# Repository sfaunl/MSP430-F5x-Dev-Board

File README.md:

MSP430-F5x-Dev-Board
====================

MSP430 5 Series Development Board

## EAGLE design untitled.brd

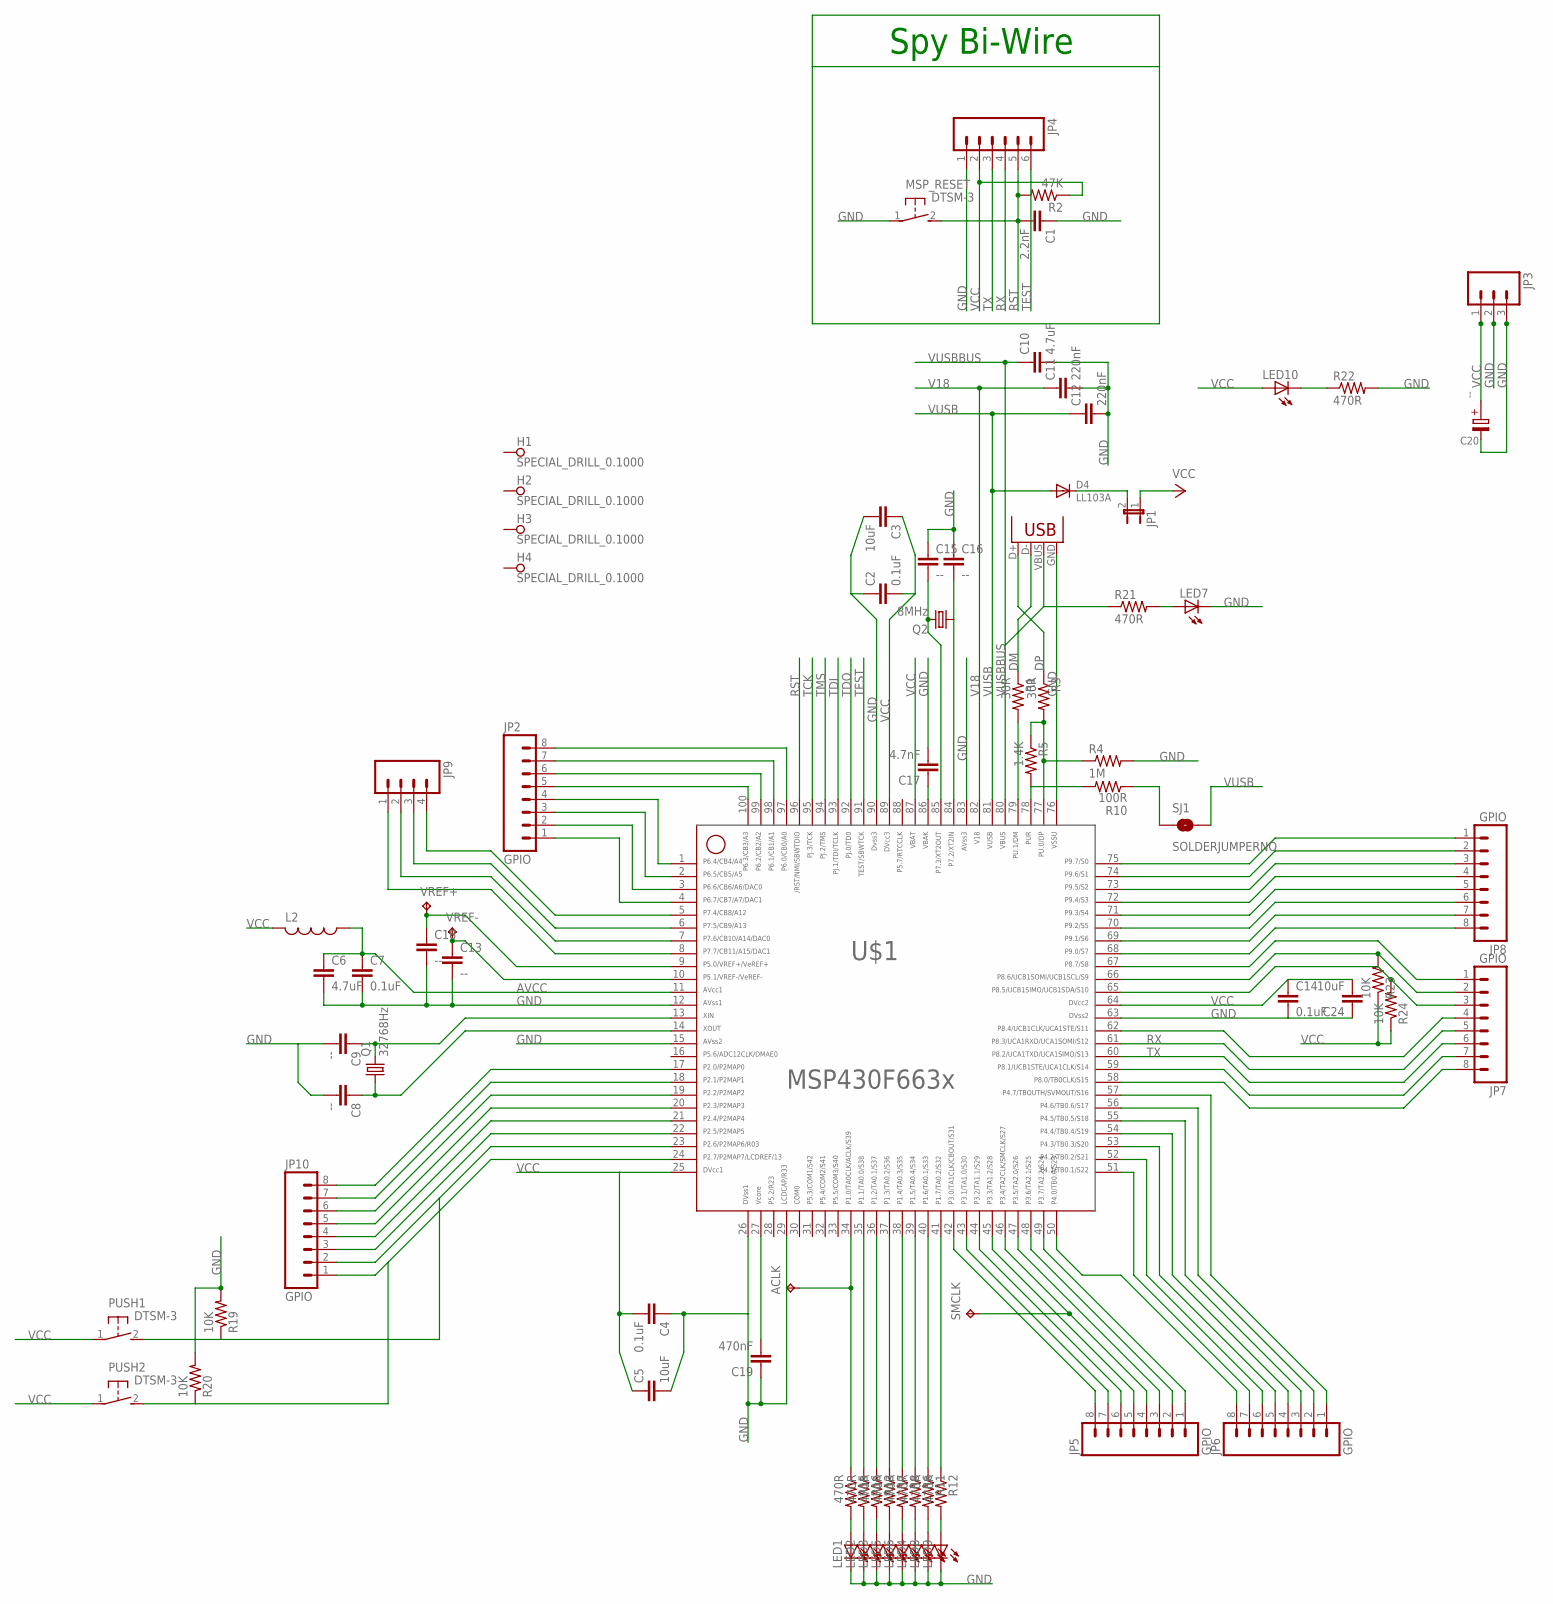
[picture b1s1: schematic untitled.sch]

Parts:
ACLK: TPB1,27; B1,27
C1: 2.2nF; 0805
C2, C4, C7, C14: 0.1uF; 0805
C3, C5, C24: 10uF; 0805
C6, C10: 4.7uF; 0805
C8, C9, C13, C15, C16, C18: --; 0805
C11, C12: 220nF; 0805
C17: 4.7nF; 0805
C19: 470nF; 0805
C20: --; 1210ELKO
D4: LL103A; SOD-80
H1, H2, H3, H4: SPECIAL_DRILL_0.1000; PAD_0.1000
JP1: JP1E; JP1
JP2, JP5, JP6, JP7, JP8, JP10: GPIO; 1X08
JP3: M03PTH; 1X03
JP4: M06SIP; 1X06
JP9: M04PTH; 1X04
L2: L-USL2012C; L2012C
LED1, LED2, LED3, LED4, LED5, LED6, LED7, LED8, LED9, LED10: LEDCHIPLED_0805; CHIPLED_0805
MSP_RESET: DTSM-3
PUSH1, PUSH2: DTSM-3
Q1: 32768Hz; TC26H
Q2: 8MHz; HC49U-V
R1, R3: 30R; M0805
R2: 47K; M0805
R4: 1M; M0805
R5: 1.4K; M0805
R6, R7, R8, R11, R12, R13, R15, R16, R21, R22: 470R; R0603
R10: 100R; R0603
R19, R20, R23, R24: 10K; M0805
SJ1: SOLDERJUMPERNO; SJ_2S-NO
SMCLK: TPB1,27; B1,27
U$1: F66XX---PZ100; PZ100
VREF+: TPB1,27; B1,27
VREF-: TPB1,27; B1,27
X1: USBSMD; USB-MINIB

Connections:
AVCC: C6.1, C7.1, L2.1, U$1.11
DM: R1.1, X1.D-
DP: R3.1, X1.D+
GND: C1.1, C2.1, C3.2, C4.1, C5.2, C6.2, C7.2, C8.2, C9.2, C10.2, C11.2, C12.2, C13.2, C14.2, C15.1, C16.1, C17.2, C18.2, C19.1, C20.-, C24.1, JP3.2, JP3.3, JP4.1, LED1.C, LED2.C, LED3.C, LED4.C, LED5.C, LED6.C, LED7.C, LED8.C, LED9.C, MSP_RESET.1, R4.2, R19.2, R20.2, R22.2, U$1.12, U$1.15, U$1.26, U$1.29, U$1.63, U$1.76, U$1.83, U$1.90, X1.GND
unnamed: R1.2, U$1.79
unnamed: R3.2, R4.1, R5.1, U$1.77
unnamed: R5.2, R10.2, U$1.78
unnamed: C9.1, Q1.2, U$1.13
unnamed: C8.1, Q1.1, U$1.14
unnamed: JP10.7, U$1.18
unnamed: R10.1, SJ1.1
unnamed: D4.2 (K), JP1.2
unnamed: R11.1, U$1.40
unnamed: C13.1, U$1.10, VREF-.TP
unnamed: LED2.A, R16.2
unnamed: C18.1, U$1.9, VREF+.TP
unnamed: R12.1, U$1.41
unnamed: C19.2, U$1.27
unnamed: R6.1, U$1.39
unnamed: R8.1, U$1.38
unnamed: R7.1, U$1.37
unnamed: JP2.5, U$1.100
unnamed: R16.1, U$1.35
unnamed: JP2.6, U$1.99
unnamed: LED4.A, R6.2
unnamed: LED3.A, R13.2
unnamed: JP2.7, U$1.98
unnamed: LED5.A, R7.2
unnamed: LED6.A, R8.2
unnamed: JP2.8, U$1.97
unnamed: JP2.4, U$1.1
unnamed: R13.1, U$1.36
unnamed: JP2.3, U$1.2
unnamed: LED1.A, R15.2
unnamed: JP2.2, U$1.3
unnamed: LED8.A, R11.2
unnamed: LED7.A, R21.2
unnamed: ACLK.TP, R15.1, U$1.34
unnamed: JP10.6, U$1.19
unnamed: LED9.A, R12.2
unnamed: JP2.1, U$1.4
unnamed: JP9.4, U$1.5
unnamed: JP9.3, U$1.6
unnamed: JP9.2, U$1.7
unnamed: JP9.1, U$1.8
unnamed: JP5.8, U$1.42
unnamed: JP5.7, U$1.43
unnamed: JP5.6, U$1.44
unnamed: JP5.5, U$1.45
unnamed: JP5.4, SMCLK.TP, U$1.46
unnamed: JP5.3, U$1.47
unnamed: JP5.2, U$1.48
unnamed: JP5.1, U$1.49
unnamed: JP6.8, U$1.50
unnamed: JP6.7, U$1.51
unnamed: JP6.6, U$1.52
unnamed: JP6.5, U$1.53
unnamed: JP6.4, U$1.54
unnamed: JP6.3, U$1.55
unnamed: JP6.2, U$1.56
unnamed: JP6.1, U$1.57
unnamed: C16.2, Q2.1, U$1.84
unnamed: C15.2, Q2.2, U$1.85
unnamed: C17.1, U$1.86
unnamed: LED10.C, R22.1
unnamed: JP10.5, U$1.20
unnamed: JP7.8, U$1.58
unnamed: JP7.7, U$1.59
unnamed: JP10.2, PUSH1.2, R19.1, U$1.23
unnamed: JP7.4, U$1.62
unnamed: JP7.3, R24.2, U$1.65
unnamed: JP7.2, R23.2, U$1.66
unnamed: JP7.1, U$1.67
unnamed: JP8.8, U$1.68
unnamed: JP8.7, U$1.69
unnamed: JP8.6, U$1.70
unnamed: JP8.5, U$1.71
unnamed: JP10.1, PUSH2.2, R20.1, U$1.24
unnamed: JP8.4, U$1.72
unnamed: JP8.3, U$1.73
unnamed: JP8.2, U$1.74
unnamed: JP8.1, U$1.75
unnamed: JP10.8, U$1.17
unnamed: JP10.4, U$1.21
unnamed: JP10.3, U$1.22
RST: C1.2, JP4.5, MSP_RESET.2, R2.2, U$1.96
RX: JP4.4, JP7.5, U$1.61
TCK: U$1.95
TDI: U$1.93
TDO: U$1.92
TEST: JP4.6, U$1.91
TMS: U$1.94
TX: JP4.3, JP7.6, U$1.60
V18: C11.1, U$1.82
VCC: C2.2, C3.1, C4.2, C5.1, C14.1, C20.+, C24.2, JP1.1, JP3.1, JP4.2, L2.2, LED10.A, PUSH1.1, PUSH2.1, R2.1, R23.1, R24.1, U$1.25, U$1.64, U$1.87, U$1.89
VUSB: C12.1, D4.1 (A), SJ1.2, U$1.81
VUSBBUS: C10.1, R21.1, U$1.80, X1.VBUS

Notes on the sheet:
Spy Bi-Wire

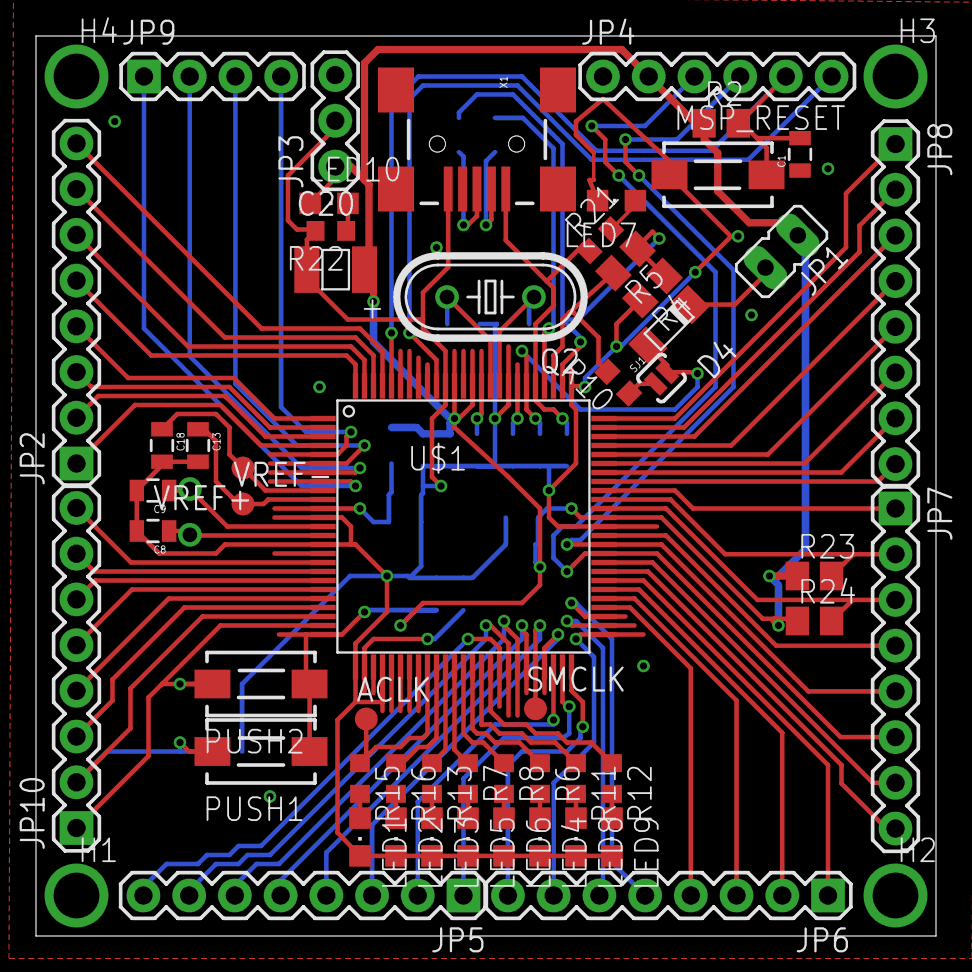
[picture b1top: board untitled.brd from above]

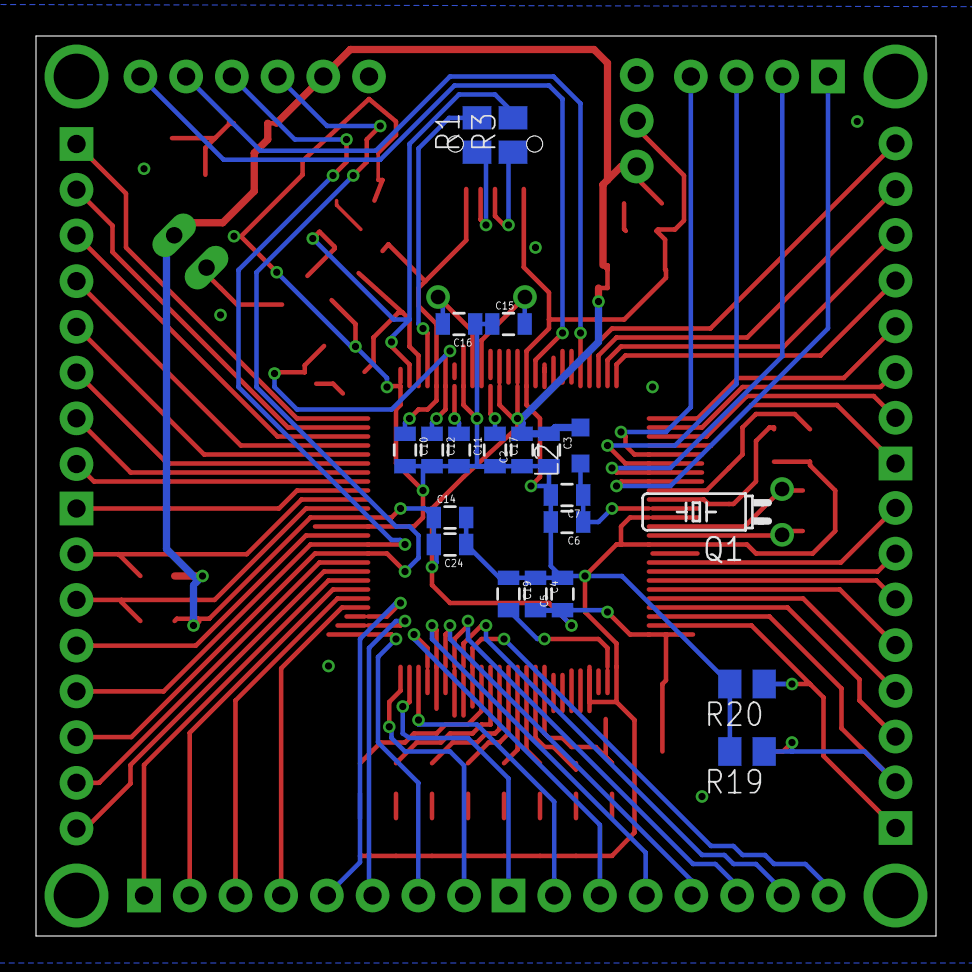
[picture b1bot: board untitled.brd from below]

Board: 2 copper layers, 50.0 x 50.0 mm, 79 parts (21 on the bottom side), 93 nets.

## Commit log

2014-03-31 First Version.
2023-01-12 remove unnecessary files
